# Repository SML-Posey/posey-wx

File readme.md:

# Posey Watch Platform

This is a simple IMU hardware platform sized to fit in a watch.

It includes:

- nRF52840 ARM microtroller with BLE radio
- CEVA BNO086 9-axis IMU
- Lithium-polymer operation and charging

## Author

[Anthony Wertz](https://me.anthonywertz.com)

## License

Shield: [![CC BY-SA 4.0][cc-by-sa-shield]][cc-by-sa]

This work is licensed under a
[Creative Commons Attribution-ShareAlike 4.0 International License][cc-by-sa].

[![CC BY-SA 4.0][cc-by-sa-image]][cc-by-sa]

[cc-by-sa]: http://creativecommons.org/licenses/by-sa/4.0/
[cc-by-sa-image]: https://licensebuttons.net/l/by-sa/4.0/88x31.png
[cc-by-sa-shield]: https://img.shields.io/badge/License-CC%20BY--SA%204.0-lightgrey.svg

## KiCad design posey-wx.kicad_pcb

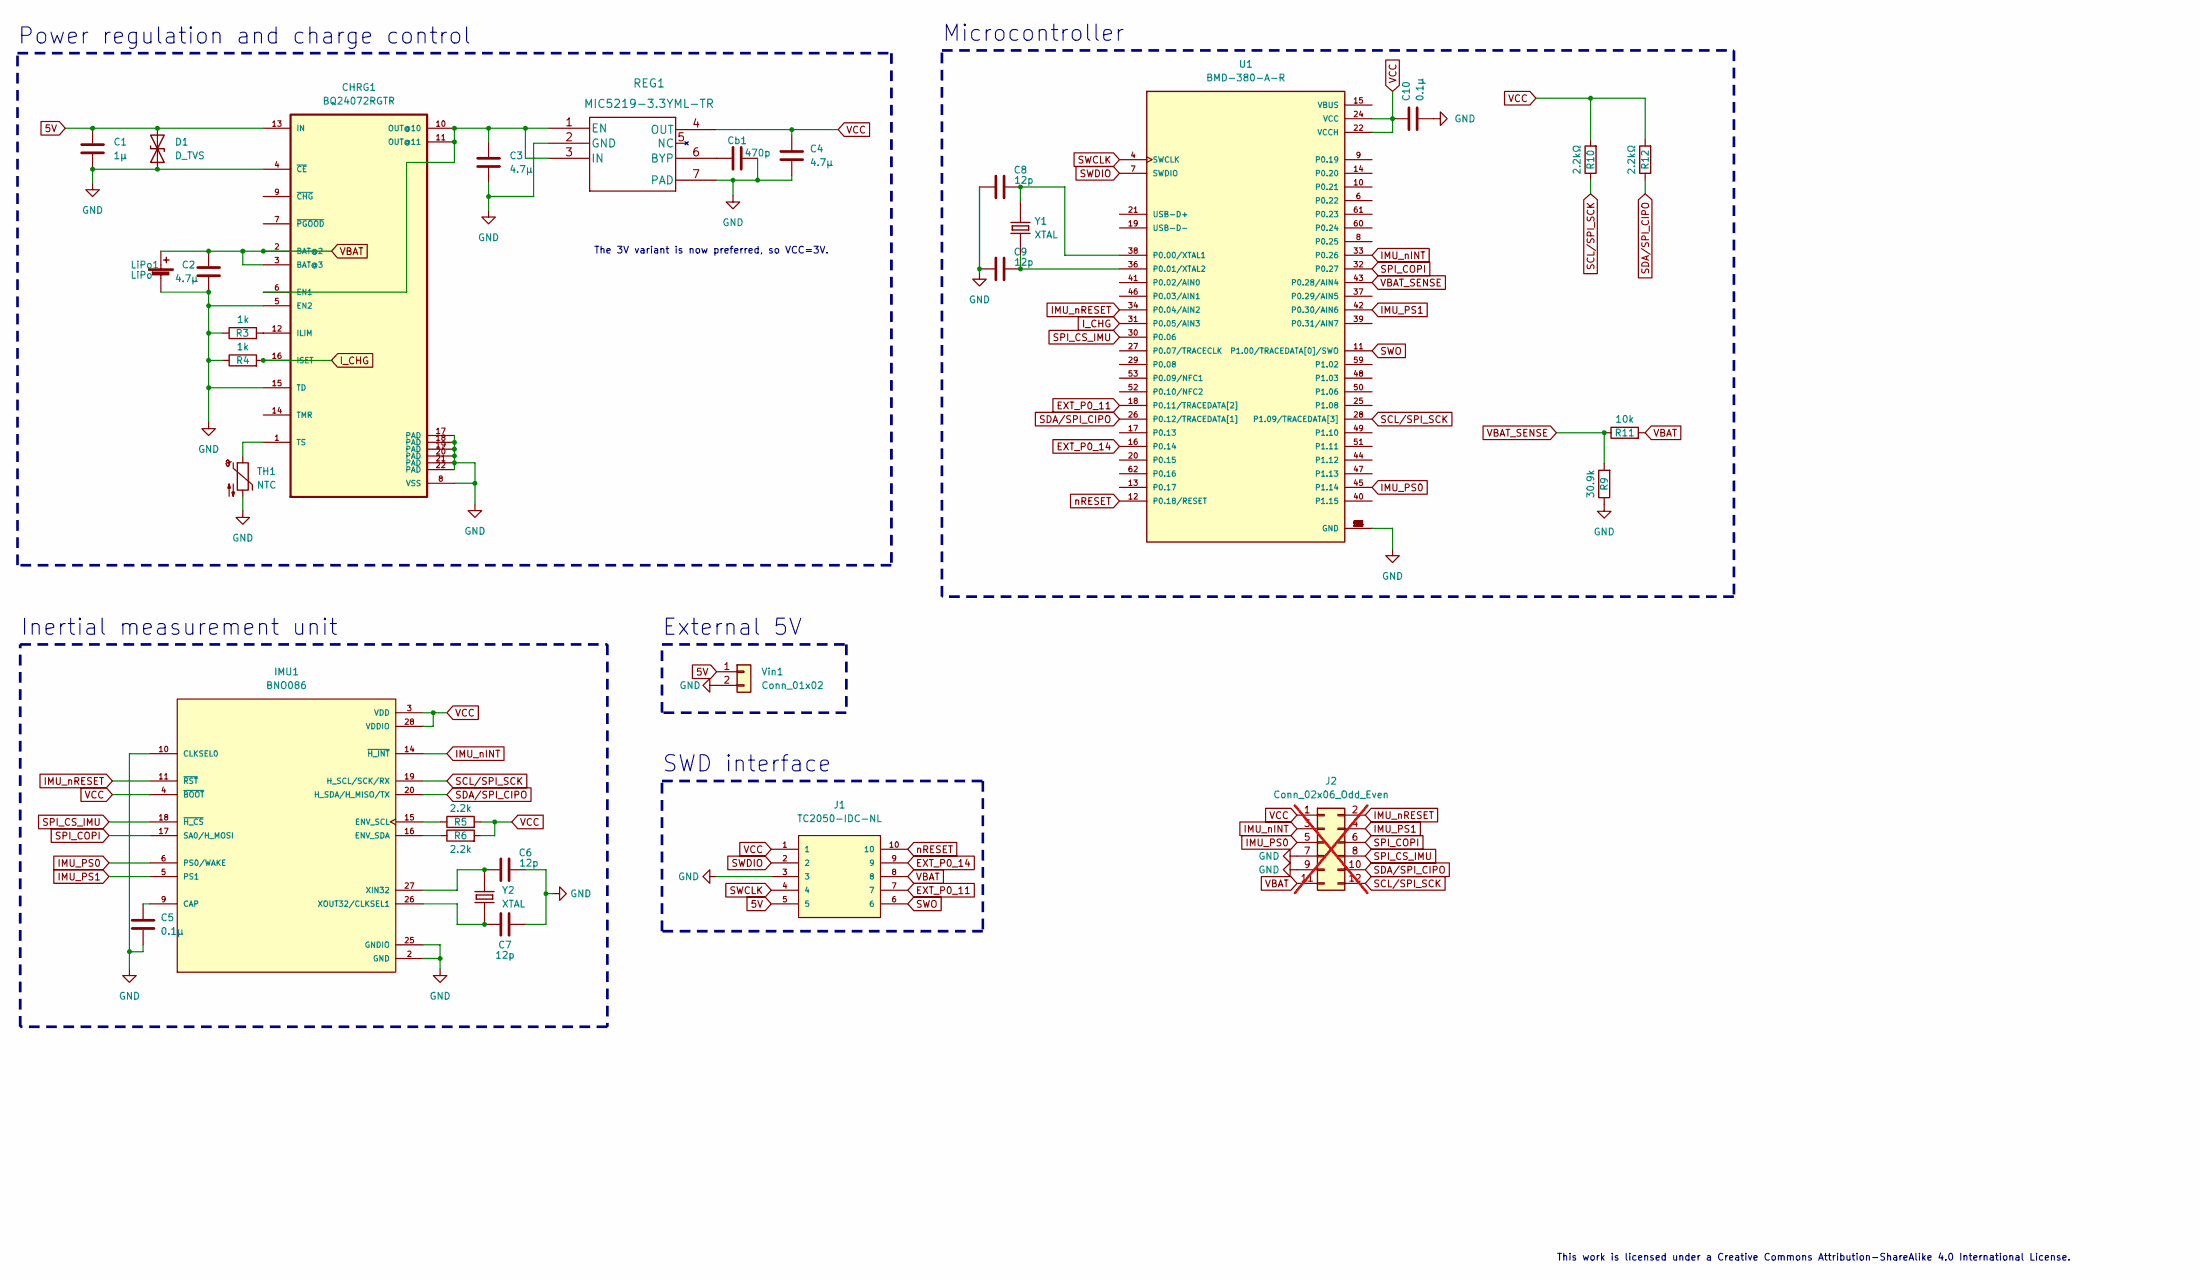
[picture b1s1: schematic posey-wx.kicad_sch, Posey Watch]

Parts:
C1: 1µ; C_0402_1005Metric
C2, C3, C4: 4.7µ; C_0402_1005Metric
C5, C10: 0.1µ; C_0402_1005Metric
C6, C7, C8, C9: 12p; C_0402_1005Metric
CHRG1: BQ24072RGTR; QFN50P300X300X100-17N
Cb1: 470p; C_0402_1005Metric
D1: D_TVS; D_0402_1005Metric
IMU1: BNO086; IC_BNO080
J1: TC2050-IDC-NL
J2: Conn_02x06_Odd_Even; PinHeader_2x06_P1.27mm_Vertical; not fitted
LiPo1: LiPo; Split Terminal 2.54
R3, R4: 1k; R_0402_1005Metric
R5, R6: 2.2k; R_0402_1005Metric
R9: 30.9k; R_0402_1005Metric
R10, R12: 2.2kΩ; R_0402_1005Metric
R11: 10k; R_0402_1005Metric
REG1: MIC5219-3.3YML-TR
TH1: NTC; R_0402_1005Metric
U1: BMD-380-A-R; XCVR_BMD-380-A-R
Vin1: Conn_01x02; Split Terminal 2.54
Y1, Y2: XTAL; XTAL_ECS-.327-9-16-TR

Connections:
5V: C1.1, CHRG1.13 (IN), D1.2 (A2), J1.5, Vin1.1
EXT_P0_11: J1.7, U1.18 (P0.11/TRACEDATA[2])
EXT_P0_14: J1.9, U1.16 (P0.14)
GND: C1.2, C2.1, C3.2, C4.2, C5.2, C6.2, C7.2, C8.1, C9.1, C10.2, CHRG1.4 (~CE), CHRG1.5 (EN2), CHRG1.8 (VSS), CHRG1.15 (TD), CHRG1.17 (PAD), CHRG1.18 (PAD), CHRG1.19 (PAD), CHRG1.20 (PAD), CHRG1.21 (PAD), CHRG1.22 (PAD), Cb1.2, D1.1 (A1), IMU1.2 (GND), IMU1.10 (CLKSEL0), IMU1.25 (GNDIO), J1.3, J2.7, J2.9, LiPo1.2 (-), R3.1, R4.1, R9.1, REG1.2 (GND), REG1.7 (PAD), TH1.2, U1.1 (GND), U1.2 (GND), U1.3 (GND), U1.5 (GND), U1.23 (GND), U1.35 (GND), U1.54 (GND), U1.55 (GND), U1.56 (GND), U1.57 (GND), U1.58 (GND), U1.63 (GND), Vin1.2
IMU_PS0: IMU1.6 (PS0/WAKE), J2.5, U1.45 (P1.14)
IMU_PS1: IMU1.5 (PS1), J2.4, U1.42 (P0.30/AIN6)
IMU_nINT: IMU1.14 (~H_INT), J2.3, U1.33 (P0.26)
IMU_nRESET: IMU1.11 (~RST), J2.2, U1.34 (P0.04/AIN2)
I_CHG: CHRG1.16 (ISET), R4.2, U1.31 (P0.05/AIN3)
unnamed: C3.1, CHRG1.6 (EN1), CHRG1.10 (OUT@10), CHRG1.11 (OUT@11), REG1.1 (EN), REG1.3 (IN)
unnamed: CHRG1.12 (ILIM), R3.2
unnamed: CHRG1.1 (TS), TH1.1
unnamed: C5.1, IMU1.9 (CAP)
unnamed: IMU1.15 (ENV_SCL), R5.1
unnamed: IMU1.16 (ENV_SDA), R6.1
unnamed: C6.1, IMU1.27 (XIN32), Y2.2
unnamed: C7.1, IMU1.26 (XOUT32/CLKSEL1), Y2.1
unnamed: Cb1.1, REG1.6 (BYP)
unnamed: C8.2, U1.38 (P0.00/XTAL1), Y1.1
unnamed: C9.2, U1.36 (P0.01/XTAL2), Y1.2
SCL/SPI_SCK: IMU1.19 (H_SCL/SCK/RX), J2.12, R10.1, U1.28 (P1.09/TRACEDATA[3])
SDA/SPI_CIPO: IMU1.20 (H_SDA/H_MISO/TX), J2.10, R12.1, U1.26 (P0.12/TRACEDATA[1])
SPI_COPI: IMU1.17 (SA0/H_MOSI), J2.6, U1.32 (P0.27)
SPI_CS_IMU: IMU1.18 (~H_CS), J2.8, U1.30 (P0.06)
SWCLK: J1.4, U1.4 (SWCLK)
SWDIO: J1.2, U1.7 (SWDIO)
SWO: J1.6, U1.11 (P1.00/TRACEDATA[0]/SWO)
VBAT: C2.2, CHRG1.2 (BAT@2), CHRG1.3 (BAT@3), J1.8, J2.11, LiPo1.1 (+), R11.2
VBAT_SENSE: R9.2, R11.1, U1.43 (P0.28/AIN4)
VCC: C4.1, C10.1, IMU1.3 (VDD), IMU1.4 (~BOOT), IMU1.28 (VDDIO), J1.1, J2.1, R5.2, R6.2, R10.2, R12.2, REG1.4 (OUT), U1.22 (VCCH), U1.24 (VCC)
nRESET: J1.10, U1.12 (P0.18/RESET)

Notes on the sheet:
Power regulation and charge control
Microcontroller
External 5V
The 3V variant is now preferred, so VCC=3V.
Inertial measurement unit
This work is licensed under a Creative Commons Attribution-ShareAlike 4.0 International License.
SWD interface

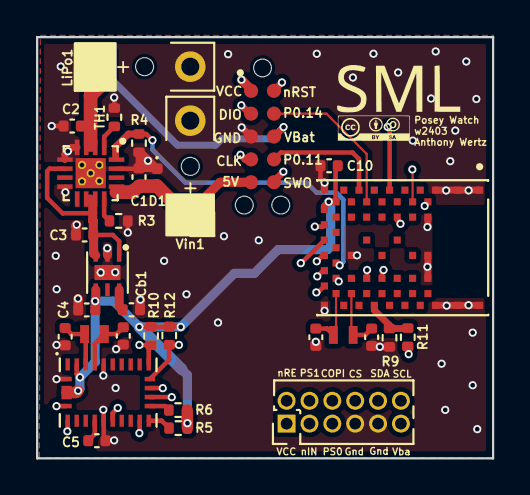
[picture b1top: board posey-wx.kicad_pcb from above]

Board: 6 copper layers, 25.3 x 23.4 mm, 31 parts (0 on the bottom side), 31 nets.

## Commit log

2023-10-24 Initial
2023-10-24 w2310
2023-10-25 w2310 µ380
2024-07-01 Updated readme, license, and version.
2024-07-01 Updated readme.
